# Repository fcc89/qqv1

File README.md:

# Quirquincho board
Small board designed to react to sound via LED strings or servos

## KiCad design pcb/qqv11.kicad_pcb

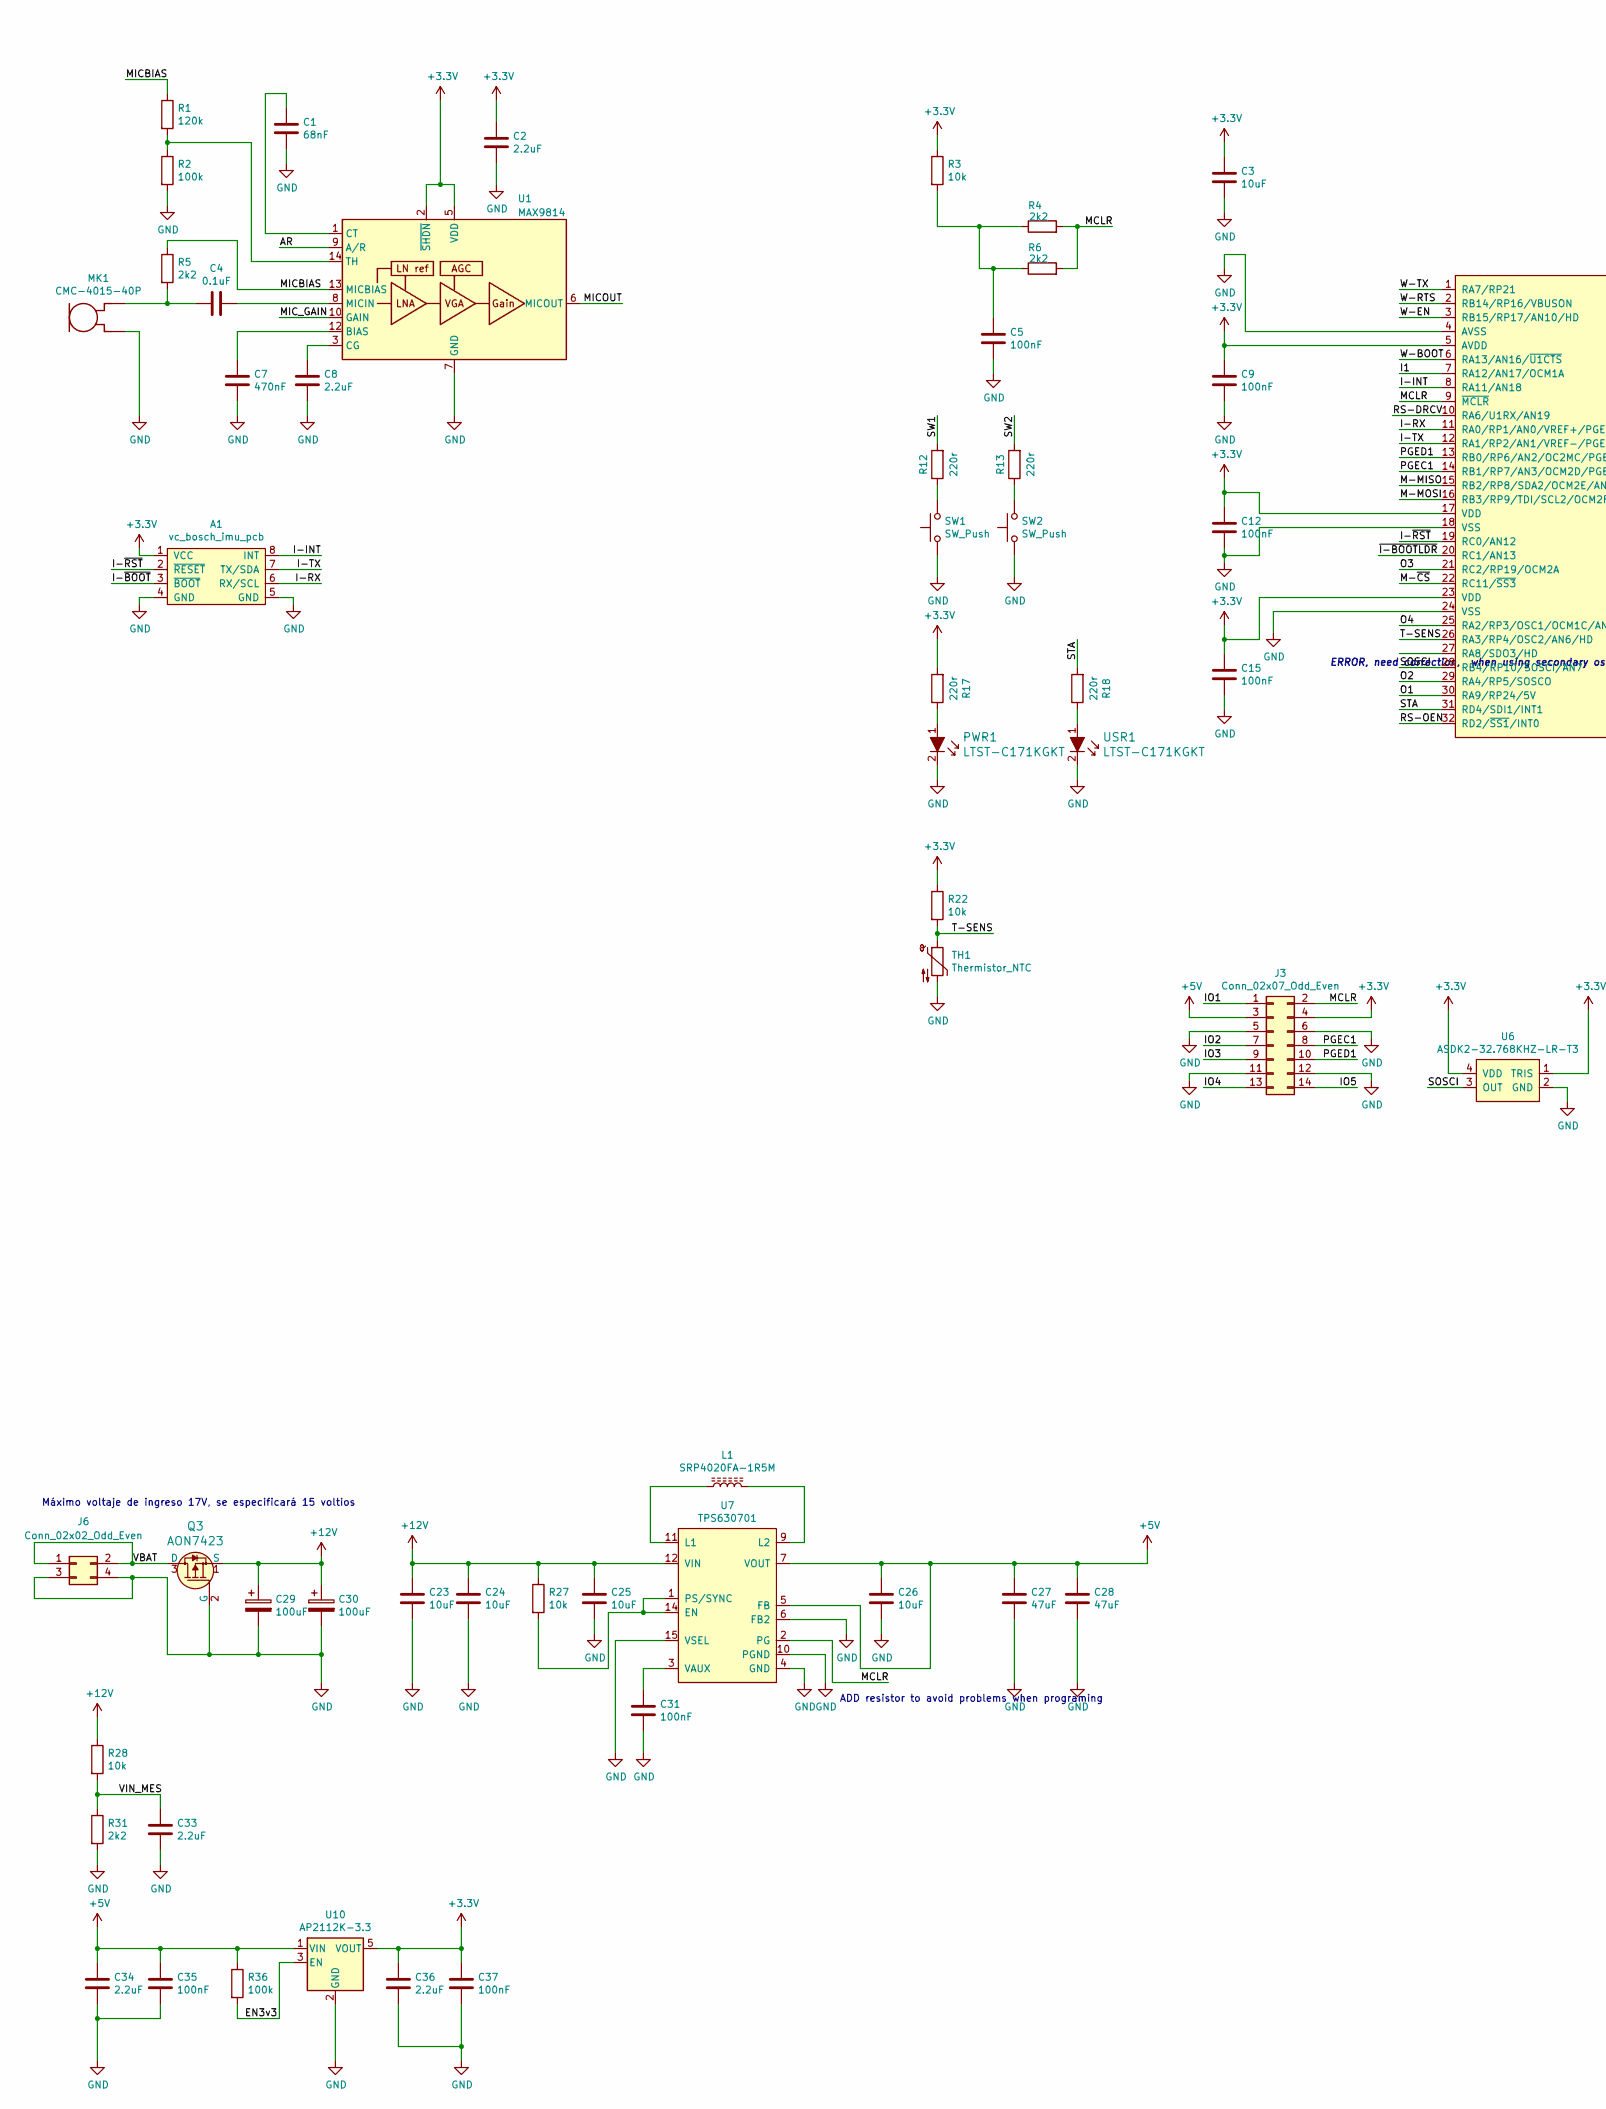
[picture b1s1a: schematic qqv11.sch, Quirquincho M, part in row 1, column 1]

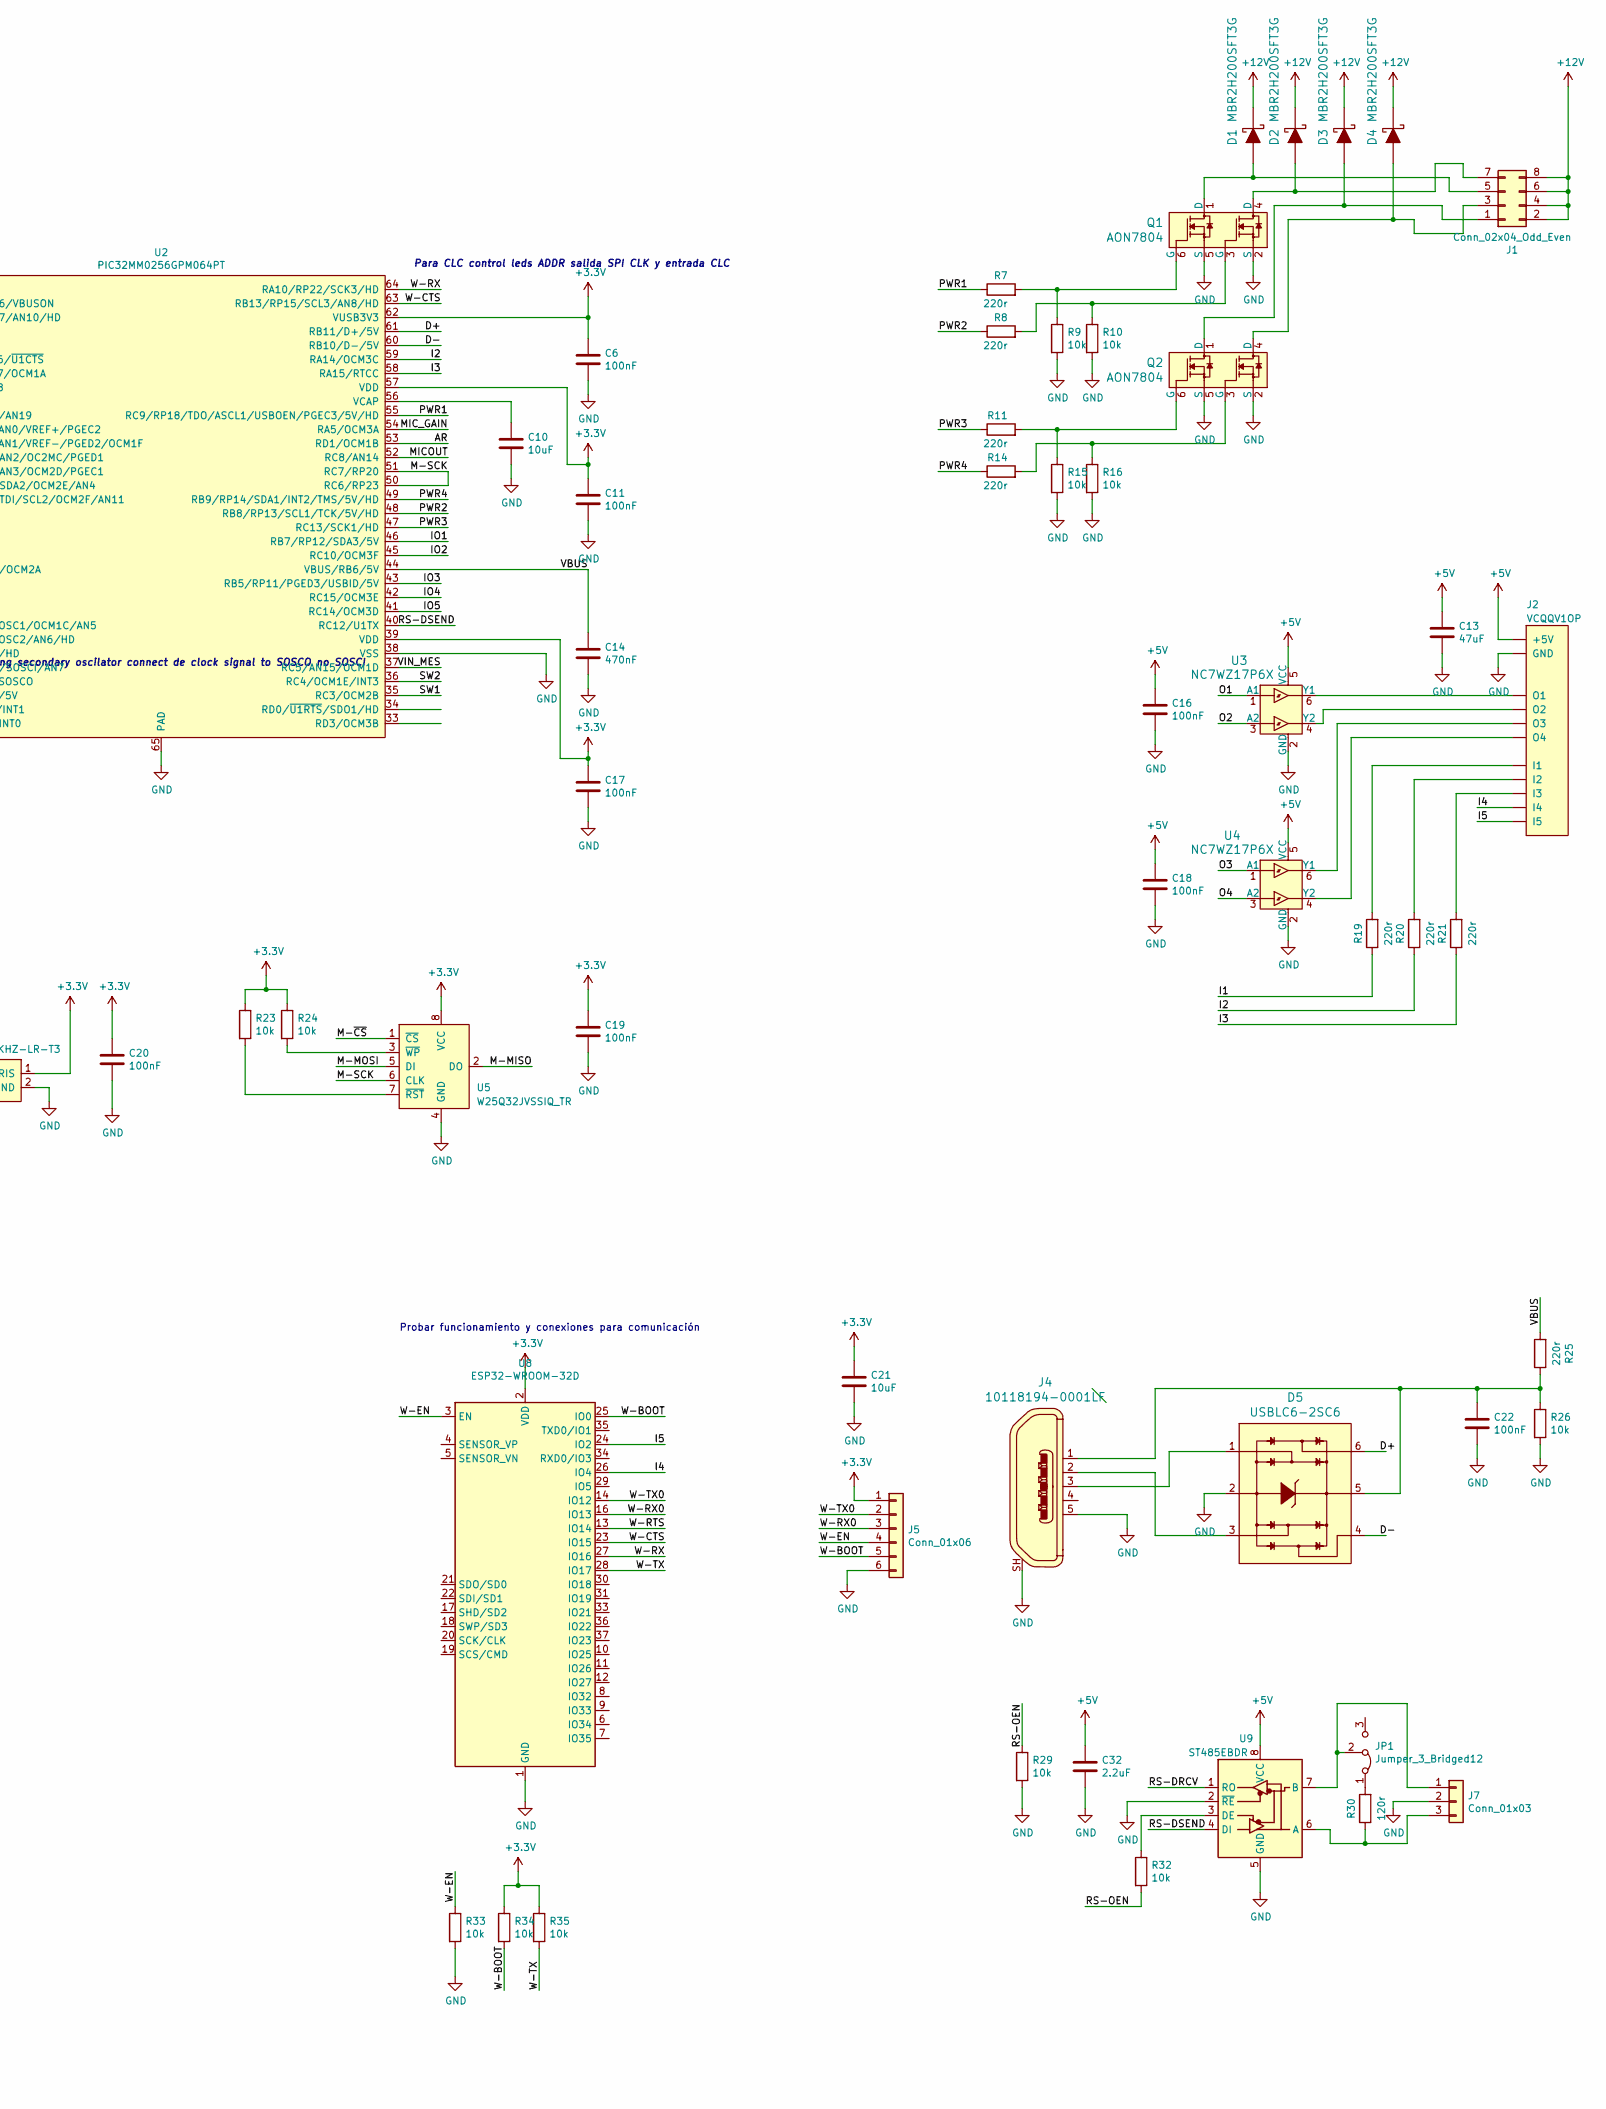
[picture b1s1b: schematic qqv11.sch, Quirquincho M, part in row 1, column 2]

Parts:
A1: vc_bosch_imu_pcb; VC_bosch_imu_pcb_mod
C1: 68nF; murata-CAP-GCM-0603-1608metric-reflow
C2, C8, C32, C33, C34, C36: 2.2uF; murata-CAP-GCM-0603-1608metric-reflow
C3, C10, C21, C23, C24: 10uF; murata-CAP-GRM-0805-2012metric-reflow
C4: 0.1uF; murata-CAP-GRM-0805-2012metric-reflow
C5, C6, C9, C11, C12, C15, C16, C17, C18, C19, C20, C22, C31, C35, C37: 100nF; murata-CAP-GCM-0603-1608metric-reflow
C7, C14: 470nF; murata-CAP-GCM-0603-1608metric-reflow
C13, C27, C28: 47uF; murata-CAP-GRM-1210-3225metric-reflow
C25, C26: 10uF; murata-CAP-GCM-0603-1608metric-reflow
C29, C30: 100uF; CP_Elec_8x6.2
D1, D2, D3, D4: MBR2H200SFT3G; onsemi-sod123fl; MPN MBR2H200SFT3G; Digi-Key_PN MBR2H200SFT3GOSCT-ND
D5: USBLC6-2SC6; SOT23-6L; MPN USBLC6-2SC6; Digi-Key_PN 497-5235-1-ND
J1: Conn_02x04_Odd_Even; PinHeader_2x04_P2.00mm_Vertical
J2: VCQQV1OP; QQv1OP
J3: Conn_02x07_Odd_Even; PinHeader_2x07_P2.54mm_Vertical
J4: 10118194-0001LF; USB_Micro_B_Female_10118194-0001LF; MPN 10118194-0001LF; Digi-Key_PN 609-4618-1-ND
J5: Conn_01x06; PinHeader_1x06_P1.00mm_Vertical
J6: Conn_02x02_Odd_Even; VC-QQV1-PWR
J7: Conn_01x03; VC-QQV1-SERIALCOM
JP1: Jumper_3_Bridged12; PinHeader_1x03_P2.00mm_Vertical
L1: ‎SRP4020FA-1R5M‎; Bourns-4020
MK1: CMC-4015-40P; MIC_CMC-4015-40P
PWR1: LTST-C171KGKT; 0805; MPN LTST-C171KGKT; Digi-Key_PN 160-1426-1-ND
Q1, Q2: AON7804; AlphaOmega3x3_8L_EP2_P; MPN AON7804; Digi-Key_PN 785-1586-1-ND
Q3: AON7423; AlphaOmega-DFN3.3x3.3-8L; MPN AON7423; Digi-Key_PN 785-1310-1-ND
R1: 120k; VC-RES-0603-1608metric
R2, R36: 100k; VC-RES-0603-1608metric
R3, R9, R10, R15, R16, R22, R23, R24, R26, R27, R28, R29, R32, R33, R34, R35: 10k; VC-RES-0603-1608metric
R4, R5, R6, R31: 2k2; VC-RES-0603-1608metric
R7, R8, R11, R12, R13, R14, R17, R18, R19, R20, R21, R25: 220r; VC-RES-0603-1608metric
R30: 120r; VC-RES-0603-1608metric
SW1, SW2: SW_Push; CK-PTS820-nopegs
TH1: Thermistor_NTC; VC-RES-0603-1608metric
U1: MAX9814; DFN-14-1EP_3x3mm_P0.4mm_EP1.78x2.35mm
U2: PIC32MM0256GPM064PT; QFN-64_EP_9x9_Pitch0.5mm
U3, U4: NC7WZ17P6X; SOT-363; MPN NC7WZ17P6X; Digi-Key_PN NC7WZ17P6XCT-ND
U5: W25Q32JVSSIQ_TR; SOIC-8_W5.6mm; MPN W25Q32JVSSIQ TR; Digi-Key_PN W25Q32JVSSIQCT-ND
U6: ASDK2-32.768KHZ-LR-T3; Abracon-ASDK-2.5x2mm
U7: TPS630701; TexasInstruments-VQFN15-RNM0015A
U8: ESP32-WROOM-32D; ESP32-WROOM-32
U9: ST485EBDR; SOIC-8_3.9x4.9mm_P1.27mm
U10: AP2112K-3.3; SOT-23-5
USR1: LTST-C171KGKT; 0805; MPN LTST-C171KGKT; Digi-Key_PN 160-1426-1-ND

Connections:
+3V3: A1.1 (VCC), C2.1, C3.1, C6.1, C9.1, C11.1, C12.1, C15.1, C17.1, C19.1, C20.1, C21.1, C36.1, C37.1, J3.4, J5.1, R3.1, R17.2, R22.1, R23.1, R24.1, R34.1, R35.1, U1.2 (~SHDN), U1.5 (VDD), U2.5 (AVDD), U2.17 (VDD), U2.23 (VDD), U2.39 (VDD), U2.57 (VDD), U2.62 (VUSB3V3), U5.8 (VCC), U6.1 (TRIS), U6.4 (VDD), U8.2 (VDD), U10.5 (VOUT)
+5V: C13.1, C16.1, C18.1, C26.1, C27.1, C28.1, C32.1, C34.1, C35.1, J2.10 (+5V), J2.11 (+5V), J2.12 (+5V), J2.13 (+5V), J3.3, R36.1, U3.5 (VCC), U4.5 (VCC), U7.5 (FB), U7.7 (VOUT), U7.8 (VOUT), U9.8 (VCC), U10.1 (VIN)
+12V: C23.1, C24.1, C25.1, C29.1, C30.1, D1.K, D2.K, D3.K, D4.K, J1.2, J1.4, J1.6, J1.8, Q3.1 (S), R27.1, R28.1, U7.12 (VIN), U7.13 (VIN)
/AR: U1.9 (A/R), U2.53 (RD1/OCM1B)
/D+: D5.6, U2.61 (RB11/D+/5V)
/D-: D5.4, U2.60 (RB10/D-/5V)
/EN3v3: R36.2, U10.3 (EN)
/I1: R19.1, U2.7 (RA12/AN17/OCM1A)
/I2: R20.1, U2.59 (RA14/OCM3C)
/I3: R21.1, U2.58 (RA15/RTCC)
/I4: J2.17 (I4), U8.26 (IO4)
/I5: J2.18 (I5), U8.24 (IO2)
/I-INT: A1.8 (INT), U2.8 (RA11/AN18)
/I-RX: A1.6 (RX/SCL), U2.11 (RA0/RP1/AN0/VREF+/PGEC2)
/I-TX: A1.7 (TX/SDA), U2.12 (RA1/RP2/AN1/VREF-/PGED2/OCM1F)
/I-~RST~: A1.2 (~RESET~), U2.19 (RC0/AN12)
/IO1: J3.1, U2.46 (RB7/RP12/SDA3/5V)
/IO2: J3.7, U2.45 (RC10/OCM3F)
/IO3: J3.9, U2.43 (RB5/RP11/PGED3/USBID/5V)
/IO4: J3.13, U2.42 (RC15/OCM3E)
/IO5: J3.14, U2.41 (RC14/OCM3D)
/M-MISO: U2.15 (RB2/RP8/SDA2/OCM2E/AN4), U5.2 (DO)
/M-MOSI: U2.16 (RB3/RP9/TDI/SCL2/OCM2F/AN11), U5.5 (DI)
/M-SCK: U2.50 (RC6/RP23), U2.51 (RC7/RP20), U5.6 (CLK)
/M-~CS~: U2.22 (RC11/~SS3~), U5.1 (~CS)
/MCLR: J3.2, R4.2, R6.2, U2.9 (~MCLR~), U7.2 (PG)
/MICBIAS: R1.1, R5.1, U1.13 (MICBIAS)
/MICOUT: U1.6 (MICOUT), U2.52 (RC8/AN14)
/MIC_GAIN: U1.10 (GAIN), U2.54 (RA5/OCM3A)
/O1: U2.30 (RA9/RP24/5V), U3.1 (A1)
/O2: U2.29 (RA4/RP5/SOSCO), U3.3 (A2)
/O3: U2.21 (RC2/RP19/OCM2A), U4.1 (A1)
/O4: U2.25 (RA2/RP3/OSC1/OCM1C/AN5), U4.3 (A2)
/PGEC1: J3.8, U2.14 (RB1/RP7/AN3/OCM2D/PGEC1)
/PGED1: J3.10, U2.13 (RB0/RP6/AN2/OC2MC/PGED1)
/PWR1: R7.1, U2.55 (RC9/RP18/TDO/ASCL1/USBOEN/PGEC3/5V/HD)
/PWR2: R8.1, U2.48 (RB8/RP13/SCL1/TCK/5V/HD)
/PWR3: R11.1, U2.47 (RC13/SCK1/HD)
/PWR4: R14.1, U2.49 (RB9/RP14/SDA1/INT2/TMS/5V/HD)
/RS-DRCV: U2.10 (RA6/U1RX/AN19), U9.1 (RO)
/RS-DSEND: U2.40 (RC12/U1TX), U9.4 (DI)
/RS-OEN: R29.1, R32.2, U2.32 (RD2/~SS1~/INT0)
/SOSCI: U2.28 (RB4/RP10/SOSCI/AN7), U6.3 (OUT)
/STA: R18.2, U2.31 (RD4/SDI1/INT1)
/SW1: R12.2, U2.35 (RC3/OCM2B)
/SW2: R13.2, U2.36 (RC4/OCM1E/INT3)
/T-SENS: R22.2, TH1.1, U2.26 (RA3/RP4/OSC2/AN6/HD)
/VBAT: J6.1, J6.2, Q3.3 (D)
/VBUS: C14.1, R25.2, U2.44 (VBUS/RB6/5V)
/VIN_MES: C33.1, R28.2, R31.1, U2.37 (RC5/AN15/OCM1D)
/W-BOOT: J5.5, R34.2, U2.6 (RA13/AN16/~U1CTS~), U8.25 (IO0)
/W-CTS: U2.63 (RB13/RP15/SCL3/AN8/HD), U8.23 (IO15)
/W-EN: J5.4, R33.1, U2.3 (RB15/RP17/AN10/HD), U8.3 (EN)
/W-RTS: U2.2 (RB14/RP16/VBUSON), U8.13 (IO14)
/W-RX: U2.64 (RA10/RP22/SCK3/HD), U8.27 (IO16)
/W-RX0: J5.3, U8.16 (IO13)
/W-TX: R35.2, U2.1 (RA7/RP21), U8.28 (IO17)
/W-TX0: J5.2, U8.14 (IO12)
GND: A1.4 (GND), A1.5 (GND), C1.2, C2.2, C3.2, C5.2, C6.2, C7.2, C8.2, C9.2, C10.2, C11.2, C12.2, C13.2, C14.2, C15.2, C16.2, C17.2, C18.2, C19.2, C20.2, C21.2, C22.2, C23.2, C24.2, C25.2, C26.2, C27.2, C28.2, C29.2, C30.2, C31.2, C32.2, C33.2, C34.2, C35.2, C36.2, C37.2, D5.2, J2.1 (GND), J2.2 (GND), J2.3 (GND), J2.4 (GND), J2.5 (GND), J2.6 (GND), J2.7 (GND), J2.8 (GND), J2.9 (GND), J3.5, J3.6, J3.11, J3.12, J4.5, J4.SH, J5.6, J6.3, J6.4, J7.2, MK1.M (GND), PWR1.2, Q1.2 (S), Q1.5 (S), Q2.2 (S), Q2.5 (S), Q3.2 (G), R2.2, R9.2, R10.2, R15.2, R16.2, R26.2, R29.2, R31.2, R33.2, SW1.1, SW2.1, TH1.2, U1.4 (GND), U1.7 (GND), U1.11 (GND), U1.15 (GND), U2.4 (AVSS), U2.18 (VSS), U2.24 (VSS), U2.38 (VSS), U2.65 (PAD), U3.2 (GND), U4.2 (GND), U5.4 (GND), U6.2 (GND), U7.4 (GND), U7.6 (FB2), U7.10 (PGND), U7.15 (VSEL), U8.1 (GND), U8.15 (GND), U8.38 (GND), U9.2 (~RE), U9.5 (GND), U10.2 (GND), USR1.2
unnamed: C1.1, U1.1 (CT)
unnamed: C4.1, U1.8 (MICIN)
unnamed: C4.2, MK1.P (OUT), R5.2
unnamed: C5.1, R3.2, R4.1, R6.1
unnamed: C7.1, U1.12 (BIAS)
unnamed: C8.1, U1.3 (CG)
unnamed: C10.1, U2.56 (VCAP)
unnamed: C22.1, D5.5, J4.1, R25.1, R26.1
unnamed: C31.1, U7.3 (VAUX)
unnamed: D1.A, J1.5, Q1.1 (D)
unnamed: D2.A, J1.7, Q1.4 (D)
unnamed: D3.A, J1.1, Q2.1 (D)
unnamed: D4.A, J1.3, Q2.4 (D)
unnamed: D5.1, J4.3
unnamed: D5.3, J4.2
unnamed: J2.14 (I1), R19.2
unnamed: J2.15 (I2), R20.2
unnamed: J2.16 (I3), R21.2
unnamed: J2.19 (O1), U3.6 (Y1)
unnamed: J2.20 (O2), U3.4 (Y2)
unnamed: J2.21 (O3), U4.6 (Y1)
unnamed: J2.22 (O4), U4.4 (Y2)
unnamed: J7.1, JP1.2 (C), U9.7 (B)
unnamed: J7.3, R30.1, U9.6 (A)
unnamed: JP1.1 (A), R30.2
unnamed: L1.1, U7.11 (L1)
unnamed: L1.2, U7.9 (L2)
unnamed: PWR1.1, R17.1
unnamed: Q1.3 (G), R8.2, R10.1
unnamed: Q1.6 (G), R7.2, R9.1
unnamed: Q2.3 (G), R14.2, R16.1
unnamed: Q2.6 (G), R11.2, R15.1
unnamed: R1.2, R2.1, U1.14 (TH)
unnamed: R12.1, SW1.2
unnamed: R13.1, SW2.2
unnamed: R18.1, USR1.1
unnamed: R23.2, U5.7 (~RST)
unnamed: R24.2, U5.3 (~WP)
unnamed: R27.2, U7.1 (PS/SYNC), U7.14 (EN)
unnamed: R32.1, U9.3 (DE)

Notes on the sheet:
Probar funcionamiento y conexiones para comunicación
Máximo voltaje de ingreso 17V, se especificará 15 voltios
Para CLC control leds ADDR salida SPI CLK y entrada CLC
ERROR, need correction, when using secondary oscilator connect de clock signal to SOSCO no SOSCI
ADD resistor to avoid problems when programing

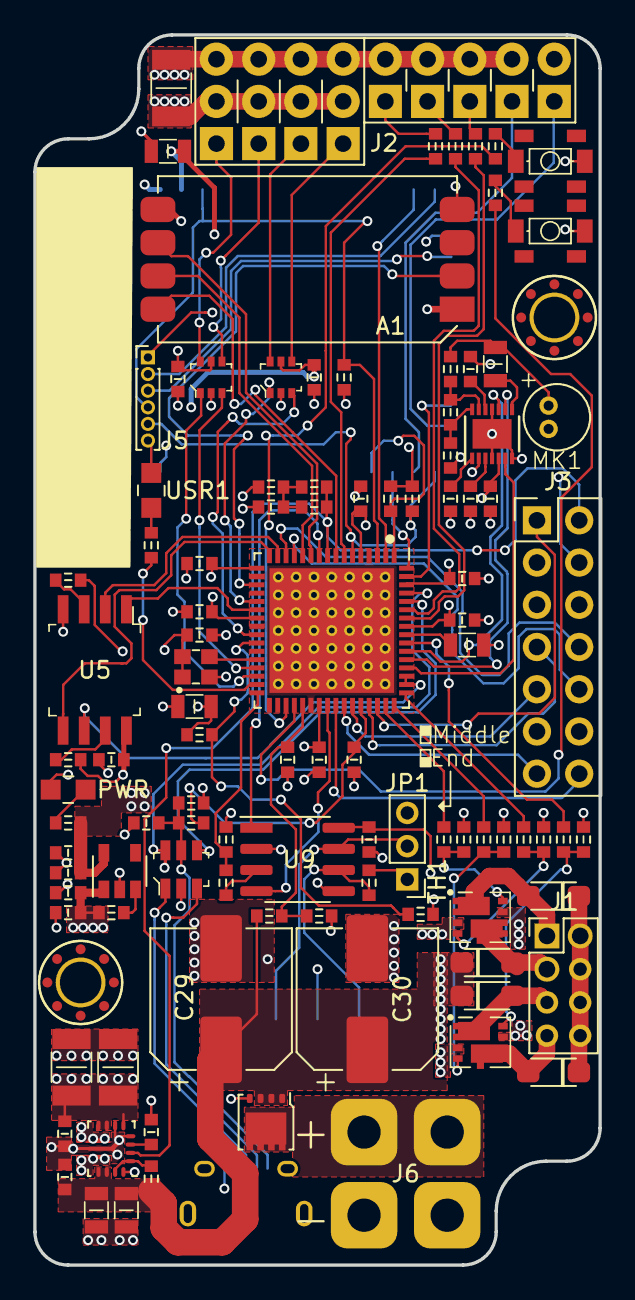
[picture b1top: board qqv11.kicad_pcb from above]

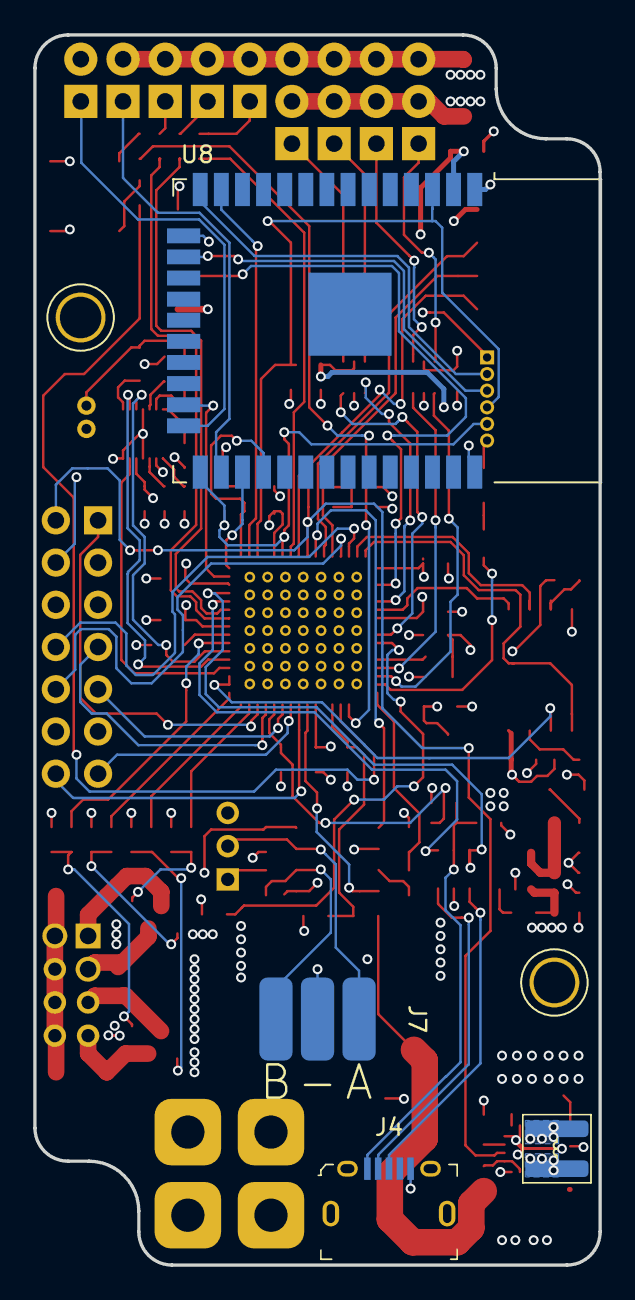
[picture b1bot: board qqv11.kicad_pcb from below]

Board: 4 copper layers, 34.0 x 74.0 mm, 107 parts (4 on the bottom side), 99 nets.

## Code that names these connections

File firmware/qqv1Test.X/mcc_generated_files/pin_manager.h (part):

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*/
/**
  @Summary
    Sets the GPIO pin, RA12, high using LATA12.

  @Description
    Sets the GPIO pin, RA12, high using LATA12.

  @Preconditions
    The RA12 must be set to an output.
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#define I1_SetHigh()          ( LATASET = (1 << 12) )
/**
  @Summary
    Sets the GPIO pin, RA12, low using LATA12.

  @Description
    Sets the GPIO pin, RA12, low using LATA12.

  @Preconditions
    The RA12 must be set to an output.
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    Sets a value to the GPIO pin.

  @Description
    Sets or Resets the GPIO pin, RA12, low or high using LATA12.

  @Preconditions
    The RA12 must be set to an output.
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
/**
  @Summary
    Toggles the GPIO pin, RA12, using LATA12.

  @Description
    Toggles the GPIO pin, RA12, using LATA12.

  @Preconditions
    The RA12 must be set to an output.
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#define I1_Toggle()           ( LATAINV = (1 << 12) )
/**
  @Summary
    Reads the value of the GPIO pin, RA12.

  @Description
    Reads the value of the GPIO pin, RA12.

  @Preconditions
    None.
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    </code>

*/
#define I1_GetValue()         PORTAbits.RA12
/**
  @Summary
    Configures the GPIO pin, RA12, as an input.

  @Description
    Configures the GPIO pin, RA12, as an input.

  @Preconditions
    None.
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#define I1_SetDigitalInput()   ( TRISASET = (1 << 12) )
/**
  @Summary
    Configures the GPIO pin, RA12, as an output.

  @Description
    Configures the GPIO pin, RA12, as an output.

  @Preconditions
    None.
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#define I1_SetDigitalOutput()   ( TRISACLR = (1 << 12) )
/**
  @Summary
    Sets the GPIO pin, RA14, high using LATA14.

  @Description
    Sets the GPIO pin, RA14, high using LATA14.

  @Preconditions
    The RA14 must be set to an output.
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#define I2_SetHigh()          ( LATASET = (1 << 14) )
/**
  @Summary
    Sets the GPIO pin, RA14, low using LATA14.

  @Description
    Sets the GPIO pin, RA14, low using LATA14.

  @Preconditions
    The RA14 must be set to an output.
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    Sets a value to the GPIO pin.

  @Description
    Sets or Resets the GPIO pin, RA14, low or high using LATA14.

  @Preconditions
    The RA14 must be set to an output.
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
/**
  @Summary
    Toggles the GPIO pin, RA14, using LATA14.

  @Description
    Toggles the GPIO pin, RA14, using LATA14.

  @Preconditions
    The RA14 must be set to an output.
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#define I2_Toggle()           ( LATAINV = (1 << 14) )
/**
  @Summary
    Reads the value of the GPIO pin, RA14.

  @Description
    Reads the value of the GPIO pin, RA14.

  @Preconditions
    None.
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    </code>

*/
#define I2_GetValue()         PORTAbits.RA14
/**
  @Summary
    Configures the GPIO pin, RA14, as an input.

  @Description
    Configures the GPIO pin, RA14, as an input.

  @Preconditions
    None.
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#define I2_SetDigitalInput()   ( TRISASET = (1 << 14) )
/**
  @Summary
    Configures the GPIO pin, RA14, as an output.

  @Description
    Configures the GPIO pin, RA14, as an output.

  @Preconditions
    None.
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#define I2_SetDigitalOutput()   ( TRISACLR = (1 << 14) )
/**
  @Summary
    Sets the GPIO pin, RA15, high using LATA15.

  @Description
    Sets the GPIO pin, RA15, high using LATA15.

  @Preconditions
    The RA15 must be set to an output.
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#define I3_SetHigh()          ( LATASET = (1 << 15) )
/**
  @Summary
    Sets the GPIO pin, RA15, low using LATA15.

  @Description
    Sets the GPIO pin, RA15, low using LATA15.

  @Preconditions
    The RA15 must be set to an output.
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    Sets a value to the GPIO pin.

  @Description
    Sets or Resets the GPIO pin, RA15, low or high using LATA15.

  @Preconditions
    The RA15 must be set to an output.
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
/**
  @Summary
    Toggles the GPIO pin, RA15, using LATA15.

  @Description
    Toggles the GPIO pin, RA15, using LATA15.

  @Preconditions
    The RA15 must be set to an output.
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#define I3_Toggle()           ( LATAINV = (1 << 15) )
/**
  @Summary
    Reads the value of the GPIO pin, RA15.

  @Description
    Reads the value of the GPIO pin, RA15.

  @Preconditions
    None.
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    </code>

*/
#define I3_GetValue()         PORTAbits.RA15
/**
  @Summary
    Configures the GPIO pin, RA15, as an input.

  @Description
    Configures the GPIO pin, RA15, as an input.

  @Preconditions
    None.
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#define I3_SetDigitalInput()   ( TRISASET = (1 << 15) )
/**
  @Summary
    Configures the GPIO pin, RA15, as an output.

  @Description
    Configures the GPIO pin, RA15, as an output.

  @Preconditions
    None.
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#define I3_SetDigitalOutput()   ( TRISACLR = (1 << 15) )
/**
  @Summary
    Sets the GPIO pin, RA3, high using LATA3.

  @Description
    Sets the GPIO pin, RA3, high using LATA3.

  @Preconditions
    The RA3 must be set to an output.
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#define T_SENSE_SetHigh()          ( LATASET = (1 << 3) )
/**
  @Summary
    Sets the GPIO pin, RA3, low using LATA3.

  @Description
    Sets the GPIO pin, RA3, low using LATA3.

  @Preconditions
    The RA3 must be set to an output.
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    Sets a value to the GPIO pin.

  @Description
    Sets or Resets the GPIO pin, RA3, low or high using LATA3.

  @Preconditions
    The RA3 must be set to an output.
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
/**
  @Summary
    Toggles the GPIO pin, RA3, using LATA3.

  @Description
    Toggles the GPIO pin, RA3, using LATA3.

  @Preconditions
    The RA3 must be set to an output.
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#define T_SENSE_Toggle()           ( LATAINV = (1 << 3) )
/**
  @Summary
    Reads the value of the GPIO pin, RA3.

  @Description
    Reads the value of the GPIO pin, RA3.

  @Preconditions
    None.
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    </code>

*/
#define T_SENSE_GetValue()         PORTAbits.RA3
/**
  @Summary
    Configures the GPIO pin, RA3, as an input.

  @Description
    Configures the GPIO pin, RA3, as an input.

  @Preconditions
    None.
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#define T_SENSE_SetDigitalInput()   ( TRISASET = (1 << 3) )
/**
  @Summary
    Configures the GPIO pin, RA3, as an output.

  @Description
    Configures the GPIO pin, RA3, as an output.

  @Preconditions
    None.
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#define T_SENSE_SetDigitalOutput()   ( TRISACLR = (1 << 3) )
/**
  @Summary
    Sets the GPIO pin, RC3, high using LATC3.

  @Description
    Sets the GPIO pin, RC3, high using LATC3.

  @Preconditions
    The RC3 must be set to an output.
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#define SW1_SetHigh()          ( LATCSET = (1 << 3) )
/**
  @Summary
    Sets the GPIO pin, RC3, low using LATC3.

  @Description
    Sets the GPIO pin, RC3, low using LATC3.

  @Preconditions
    The RC3 must be set to an output.
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    Sets a value to the GPIO pin.

  @Description
    Sets or Resets the GPIO pin, RC3, low or high using LATC3.

  @Preconditions
    The RC3 must be set to an output.
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
/**
  @Summary
    Toggles the GPIO pin, RC3, using LATC3.

  @Description
    Toggles the GPIO pin, RC3, using LATC3.

  @Preconditions
    The RC3 must be set to an output.
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#define SW1_Toggle()           ( LATCINV = (1 << 3) )
/**
  @Summary
    Reads the value of the GPIO pin, RC3.

  @Description
    Reads the value of the GPIO pin, RC3.

  @Preconditions
    None.
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    </code>

*/
#define SW1_GetValue()         PORTCbits.RC3
/**
  @Summary
    Configures the GPIO pin, RC3, as an input.

  @Description
    Configures the GPIO pin, RC3, as an input.

  @Preconditions
    None.
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#define SW1_SetDigitalInput()   ( TRISCSET = (1 << 3) )
/**
  @Summary
    Configures the GPIO pin, RC3, as an output.

  @Description
    Configures the GPIO pin, RC3, as an output.

  @Preconditions
    None.
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#define SW1_SetDigitalOutput()   ( TRISCCLR = (1 << 3) )
/**
  @Summary
    Sets the GPIO pin, RC4, high using LATC4.

  @Description
    Sets the GPIO pin, RC4, high using LATC4.

  @Preconditions
    The RC4 must be set to an output.
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#define SW2_SetHigh()          ( LATCSET = (1 << 4) )
/**
  @Summary
    Sets the GPIO pin, RC4, low using LATC4.

  @Description
    Sets the GPIO pin, RC4, low using LATC4.

  @Preconditions
    The RC4 must be set to an output.
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    Sets a value to the GPIO pin.

  @Description
    Sets or Resets the GPIO pin, RC4, low or high using LATC4.

  @Preconditions
    The RC4 must be set to an output.
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
/**
  @Summary
    Toggles the GPIO pin, RC4, using LATC4.

  @Description
    Toggles the GPIO pin, RC4, using LATC4.

  @Preconditions
    The RC4 must be set to an output.
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#define SW2_Toggle()           ( LATCINV = (1 << 4) )
/**
  @Summary
    Reads the value of the GPIO pin, RC4.

  @Description
    Reads the value of the GPIO pin, RC4.

  @Preconditions
    None.
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    </code>

*/
#define SW2_GetValue()         PORTCbits.RC4
/**
  @Summary
    Configures the GPIO pin, RC4, as an input.

  @Description
    Configures the GPIO pin, RC4, as an input.

  @Preconditions
    None.
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#define SW2_SetDigitalInput()   ( TRISCSET = (1 << 4) )
/**
  @Summary
    Configures the GPIO pin, RC4, as an output.

  @Description
    Configures the GPIO pin, RC4, as an output.

  @Preconditions
    None.
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#define SW2_SetDigitalOutput()   ( TRISCCLR = (1 << 4) )
/**
  @Summary
    Sets the GPIO pin, RC5, high using LATC5.

  @Description
    Sets the GPIO pin, RC5, high using LATC5.

  @Preconditions
    The RC5 must be set to an output.
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#define VIN_MES_SetHigh()          ( LATCSET = (1 << 5) )
/**
  @Summary
    Sets the GPIO pin, RC5, low using LATC5.

  @Description
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
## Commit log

2019-09-27 first upload
2019-11-24 Added pdf schematic and pcb
2020-01-03 added pictures
2020-03-08 revised

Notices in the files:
firmware/qqv1Test.X/mcc_generated_files/pin_manager.h:
(c) 2019 Microchip Technology Inc. and its subsidiaries. You may use this
